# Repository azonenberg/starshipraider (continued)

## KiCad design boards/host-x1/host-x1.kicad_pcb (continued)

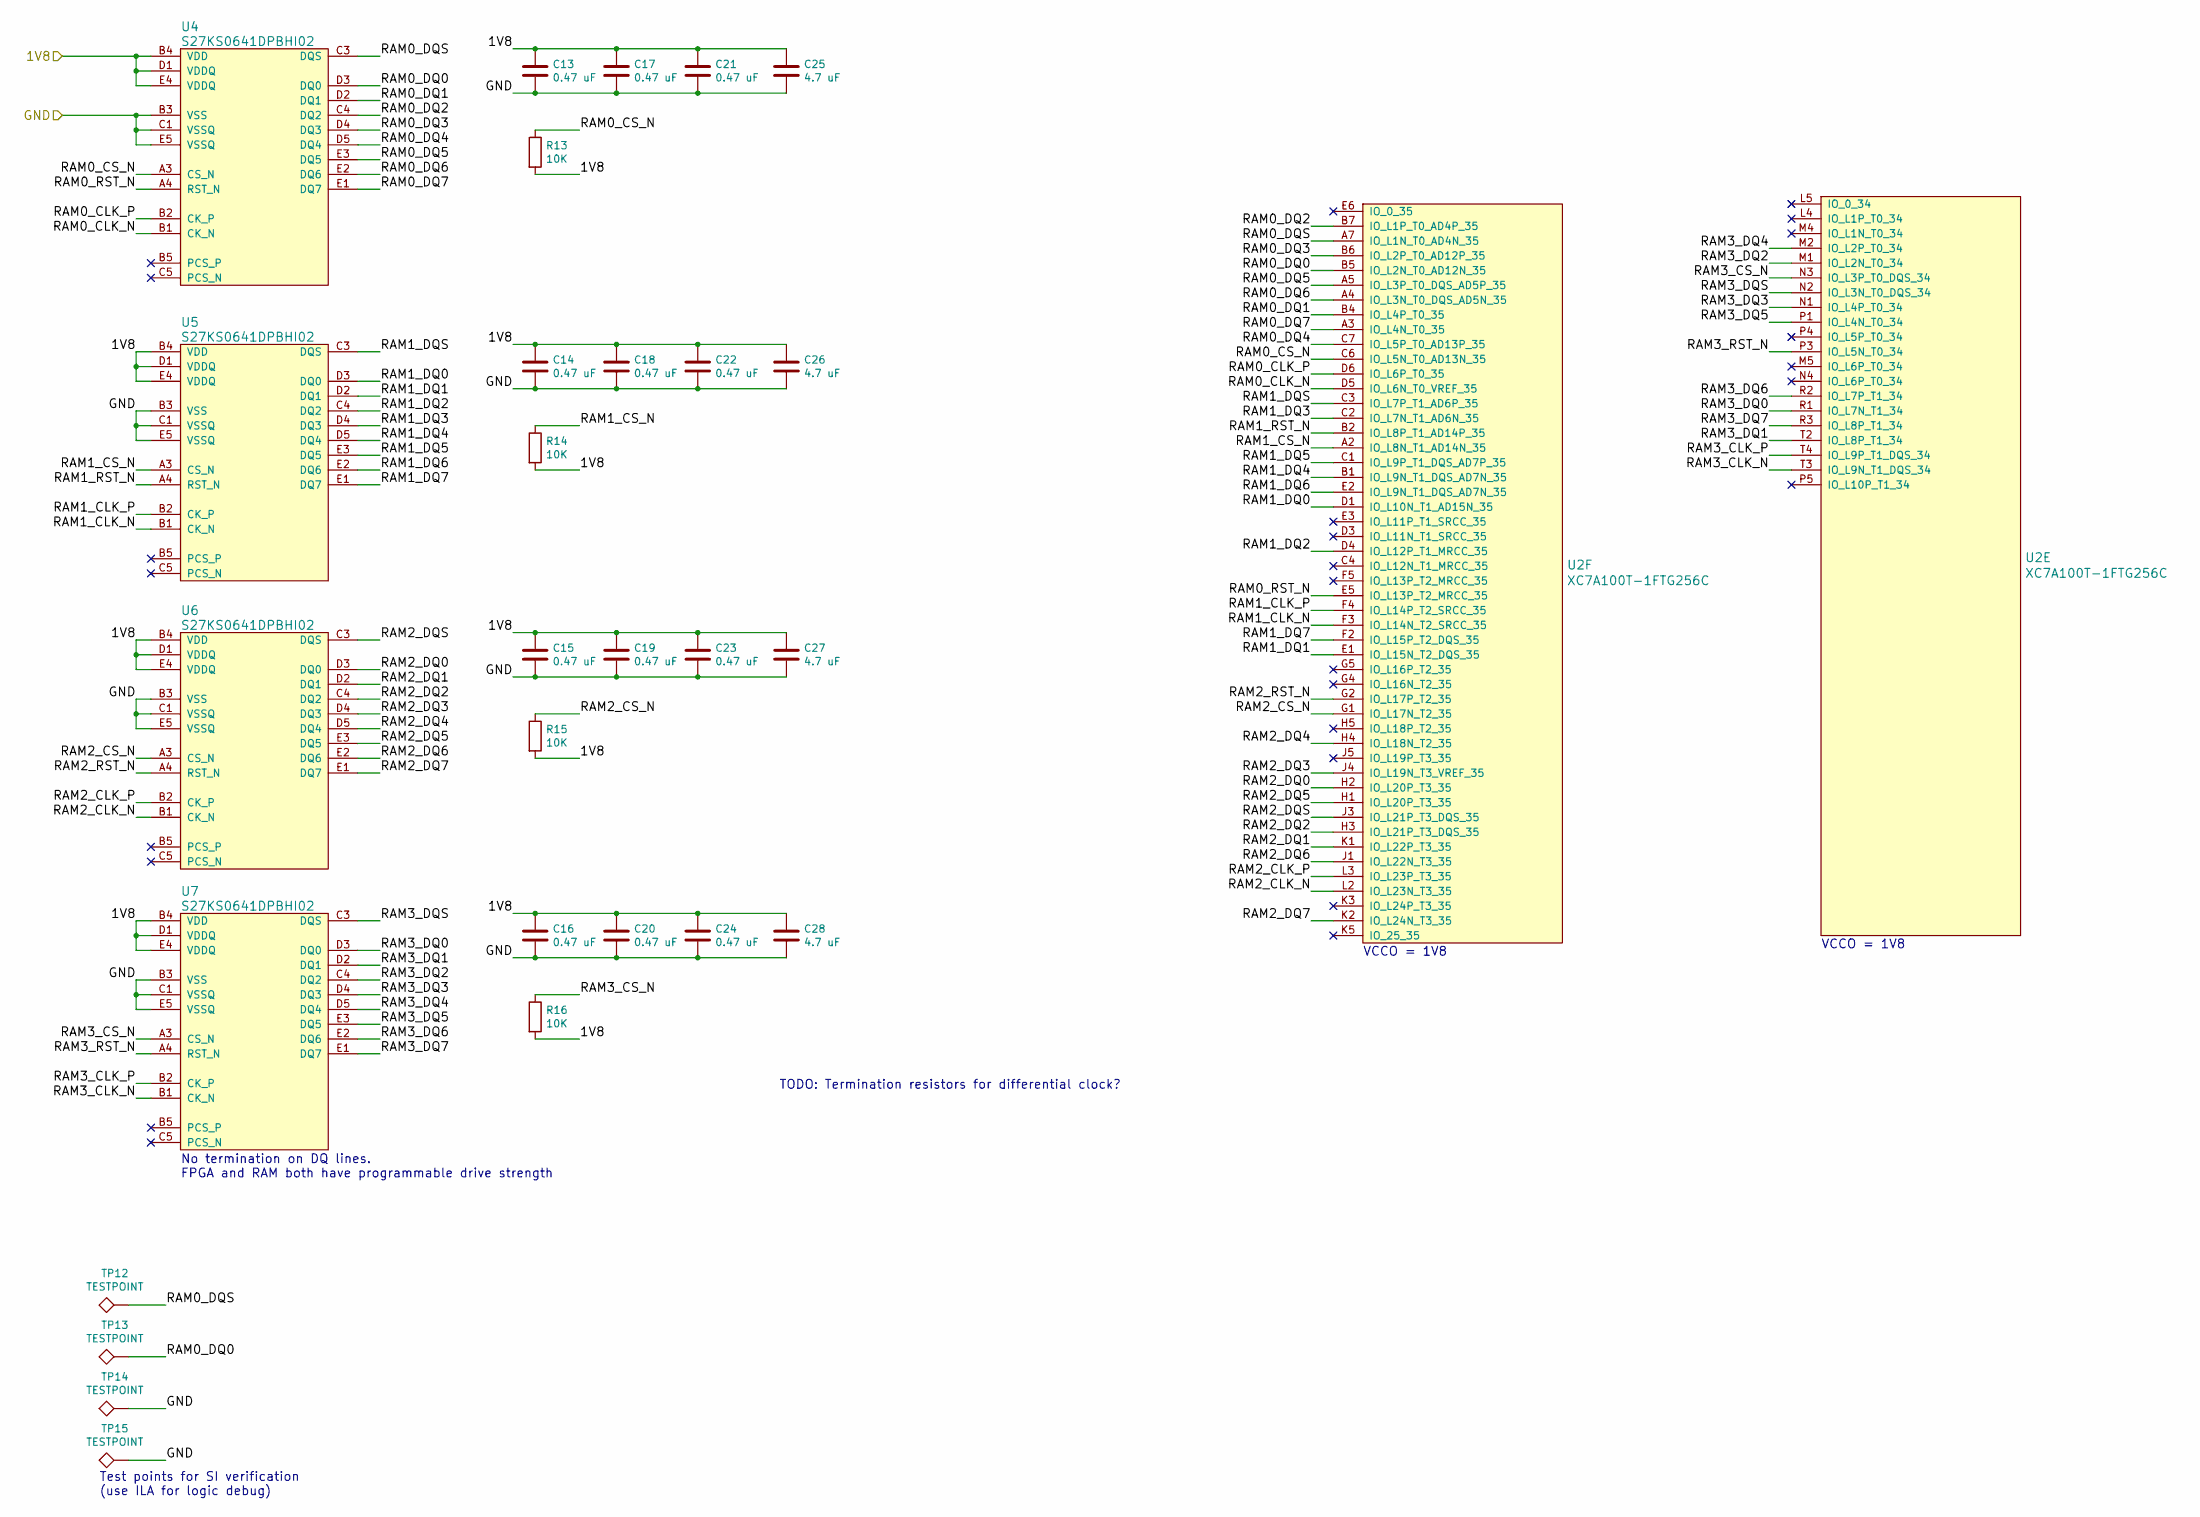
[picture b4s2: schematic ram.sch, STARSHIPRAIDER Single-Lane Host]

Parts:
C13, C14, C15, C16, C17, C18, C19, C20, C21, C22, C23, C24: 0.47 uF; EIA_0402_CAP_NOSILK
C25, C26, C27, C28: 4.7 uF; EIA_0603_CAP_NOSILK
R13, R14, R15, R16: 10K; EIA_0402_RES_NOSILK
TP12, TP13, TP14, TP15: TESTPOINT; TESTPOINT_BARETRACE_150UM
U2: XC7A100T-1FTG256C; BGA_256_17x17_FULLARRAY_1MM
U4, U5, U6, U7: S27KS0641DPBHI02; BGA_24_6x8_DEPOP1_1MM

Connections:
/1V8: C13.1, C14.1, C15.1, C16.1, C17.1, C18.1, C19.1, C20.1, C21.1, C22.1, C23.1, C24.1, C25.1, C26.1, C27.1, C28.1, R13.2, R14.2, R15.2, R16.2, U4.B4 (VDD), U4.D1 (VDDQ), U4.E4 (VDDQ), U5.B4 (VDD), U5.D1 (VDDQ), U5.E4 (VDDQ), U6.B4 (VDD), U6.D1 (VDDQ), U6.E4 (VDDQ), U7.B4 (VDD), U7.D1 (VDDQ), U7.E4 (VDDQ); also elsewhere on the board
/GND: C13.2, C14.2, C15.2, C16.2, C17.2, C18.2, C19.2, C20.2, C21.2, C22.2, C23.2, C24.2, C25.2, C26.2, C27.2, C28.2, TP14.1, TP15.1, U4.B3 (VSS), U4.C1 (VSSQ), U4.E5 (VSSQ), U5.B3 (VSS), U5.C1 (VSSQ), U5.E5 (VSSQ), U6.B3 (VSS), U6.C1 (VSSQ), U6.E5 (VSSQ), U7.B3 (VSS), U7.C1 (VSSQ), U7.E5 (VSSQ); also elsewhere on the board
/RAM/RAM0_CLK_N: U2.D5 (IO_L6N_T0_VREF_35), U4.B1 (CK_N)
/RAM/RAM0_CLK_P: U2.D6 (IO_L6P_T0_35), U4.B2 (CK_P)
/RAM/RAM0_CS_N: R13.1, U2.C6 (IO_L5N_T0_AD13N_35), U4.A3 (CS_N)
/RAM/RAM0_DQ0: TP13.1, U2.B5 (IO_L2N_T0_AD12N_35), U4.D3 (DQ0)
/RAM/RAM0_DQ1: U2.B4 (IO_L4P_T0_35), U4.D2 (DQ1)
/RAM/RAM0_DQ2: U2.B7 (IO_L1P_T0_AD4P_35), U4.C4 (DQ2)
/RAM/RAM0_DQ3: U2.B6 (IO_L2P_T0_AD12P_35), U4.D4 (DQ3)
/RAM/RAM0_DQ4: U2.C7 (IO_L5P_T0_AD13P_35), U4.D5 (DQ4)
/RAM/RAM0_DQ5: U2.A5 (IO_L3P_T0_DQS_AD5P_35), U4.E3 (DQ5)
/RAM/RAM0_DQ6: U2.A4 (IO_L3N_T0_DQS_AD5N_35), U4.E2 (DQ6)
/RAM/RAM0_DQ7: U2.A3 (IO_L4N_T0_35), U4.E1 (DQ7)
/RAM/RAM0_DQS: TP12.1, U2.A7 (IO_L1N_T0_AD4N_35), U4.C3 (DQS)
/RAM/RAM0_RST_N: U2.E5 (IO_L13P_T2_MRCC_35), U4.A4 (RST_N)
/RAM/RAM1_CLK_N: U2.F3 (IO_L14N_T2_SRCC_35), U5.B1 (CK_N)
/RAM/RAM1_CLK_P: U2.F4 (IO_L14P_T2_SRCC_35), U5.B2 (CK_P)
/RAM/RAM1_CS_N: R14.1, U2.A2 (IO_L8N_T1_AD14N_35), U5.A3 (CS_N)
/RAM/RAM1_DQ0: U2.D1 (IO_L10N_T1_AD15N_35), U5.D3 (DQ0)
/RAM/RAM1_DQ1: U2.E1 (IO_L15N_T2_DQS_35), U5.D2 (DQ1)
/RAM/RAM1_DQ2: U2.D4 (IO_L12P_T1_MRCC_35), U5.C4 (DQ2)
/RAM/RAM1_DQ3: U2.C2 (IO_L7N_T1_AD6N_35), U5.D4 (DQ3)
/RAM/RAM1_DQ4: U2.B1 (IO_L9N_T1_DQS_AD7N_35), U5.D5 (DQ4)
/RAM/RAM1_DQ5: U2.C1 (IO_L9P_T1_DQS_AD7P_35), U5.E3 (DQ5)
/RAM/RAM1_DQ6: U2.E2 (IO_L9N_T1_DQS_AD7N_35), U5.E2 (DQ6)
/RAM/RAM1_DQ7: U2.F2 (IO_L15P_T2_DQS_35), U5.E1 (DQ7)
/RAM/RAM1_DQS: U2.C3 (IO_L7P_T1_AD6P_35), U5.C3 (DQS)
/RAM/RAM1_RST_N: U2.B2 (IO_L8P_T1_AD14P_35), U5.A4 (RST_N)
/RAM/RAM2_CLK_N: U2.L2 (IO_L23N_T3_35), U6.B1 (CK_N)
/RAM/RAM2_CLK_P: U2.L3 (IO_L23P_T3_35), U6.B2 (CK_P)
/RAM/RAM2_CS_N: R15.1, U2.G1 (IO_L17N_T2_35), U6.A3 (CS_N)
/RAM/RAM2_DQ0: U2.H2 (IO_L20P_T3_35), U6.D3 (DQ0)
/RAM/RAM2_DQ1: U2.K1 (IO_L22P_T3_35), U6.D2 (DQ1)
/RAM/RAM2_DQ2: U2.H3 (IO_L21P_T3_DQS_35), U6.C4 (DQ2)
/RAM/RAM2_DQ3: U2.J4 (IO_L19N_T3_VREF_35), U6.D4 (DQ3)
/RAM/RAM2_DQ4: U2.H4 (IO_L18N_T2_35), U6.D5 (DQ4)
/RAM/RAM2_DQ5: U2.H1 (IO_L20P_T3_35), U6.E3 (DQ5)
/RAM/RAM2_DQ6: U2.J1 (IO_L22N_T3_35), U6.E2 (DQ6)
/RAM/RAM2_DQ7: U2.K2 (IO_L24N_T3_35), U6.E1 (DQ7)
/RAM/RAM2_DQS: U2.J3 (IO_L21P_T3_DQS_35), U6.C3 (DQS)
/RAM/RAM2_RST_N: U2.G2 (IO_L17P_T2_35), U6.A4 (RST_N)
/RAM/RAM3_CLK_N: U2.T3 (IO_L9N_T1_DQS_34), U7.B1 (CK_N)
/RAM/RAM3_CLK_P: U2.T4 (IO_L9P_T1_DQS_34), U7.B2 (CK_P)
/RAM/RAM3_CS_N: R16.1, U2.N3 (IO_L3P_T0_DQS_34), U7.A3 (CS_N)
/RAM/RAM3_DQ0: U2.R1 (IO_L7N_T1_34), U7.D3 (DQ0)
/RAM/RAM3_DQ1: U2.T2 (IO_L8P_T1_34), U7.D2 (DQ1)
/RAM/RAM3_DQ2: U2.M1 (IO_L2N_T0_34), U7.C4 (DQ2)
/RAM/RAM3_DQ3: U2.N1 (IO_L4P_T0_34), U7.D4 (DQ3)
/RAM/RAM3_DQ4: U2.M2 (IO_L2P_T0_34), U7.D5 (DQ4)
/RAM/RAM3_DQ5: U2.P1 (IO_L4N_T0_34), U7.E3 (DQ5)
/RAM/RAM3_DQ6: U2.R2 (IO_L7P_T1_34), U7.E2 (DQ6)
/RAM/RAM3_DQ7: U2.R3 (IO_L8P_T1_34), U7.E1 (DQ7)
/RAM/RAM3_DQS: U2.N2 (IO_L3N_T0_DQS_34), U7.C3 (DQS)
/RAM/RAM3_RST_N: U2.P3 (IO_L5N_T0_34), U7.A4 (RST_N)

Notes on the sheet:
VCCO = 1V8
No termination on DQ lines. FPGA and RAM both have programmable drive strength
Test points for SI verification (use ILA for logic debug)
TODO: Termination resistors for differential clock?

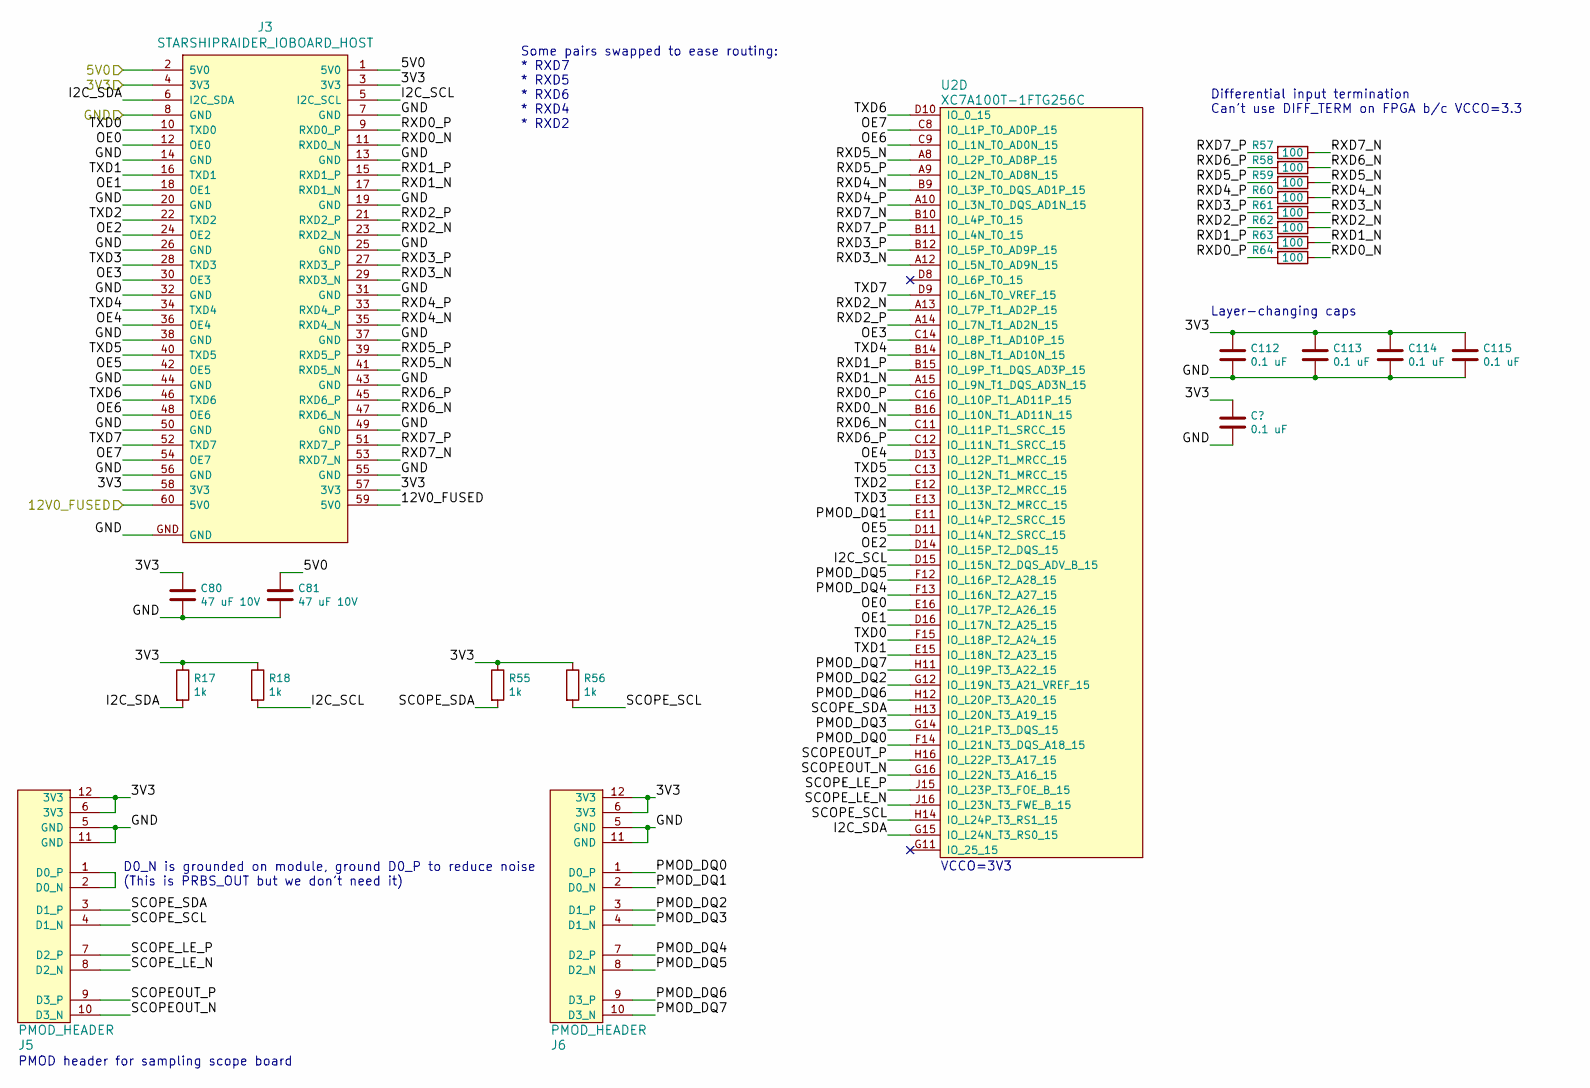
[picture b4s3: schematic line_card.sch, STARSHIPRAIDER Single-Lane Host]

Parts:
C80, C81: 47 uF 10V; EIA_1210_CAP_NOSILK
C112, C113, C114, C115: 0.1 uF; EIA_0402_CAP_NOSILK
J3: STARSHIPRAIDER_IOBOARD_HOST; CONN_SAMTEC_QTH-030-01-L-D-A
J5, J6: PMOD_HEADER; CONN_HEADER_2.54MM_2x6_RA_PMOD_HOST
R17, R18, R55, R56: 1k; EIA_0402_RES_NOSILK
R57, R58, R59, R60, R61, R62, R63, R64: 100; EIA_0201_RES_NOSILK
U2: XC7A100T-1FTG256C; BGA_256_17x17_FULLARRAY_1MM

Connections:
/3V3: C80.1, C112.1, C113.1, C114.1, C115.1, J3.3 (3V3), J3.4 (3V3), J3.57 (3V3), J3.58 (3V3), J5.6 (3V3), J5.12 (3V3), J6.6 (3V3), J6.12 (3V3), R17.1, R18.1, R55.1, R56.1; also elsewhere on the board
/5V0: C81.1, J3.1 (5V0), J3.2 (5V0); also elsewhere on the board
/12V0_FUSED: J3.59 (5V0), J3.60 (5V0); also elsewhere on the board
/GND: C80.2, C81.2, C112.2, C113.2, C114.2, C115.2, J3.7 (GND), J3.8 (GND), J3.13 (GND), J3.14 (GND), J3.19 (GND), J3.20 (GND), J3.25 (GND), J3.26 (GND), J3.31 (GND), J3.32 (GND), J3.37 (GND), J3.38 (GND), J3.43 (GND), J3.44 (GND), J3.49 (GND), J3.50 (GND), J3.55 (GND), J3.56 (GND), J3.GND, J5.5 (GND), J5.11 (GND), J6.5 (GND), J6.11 (GND); also elsewhere on the board
/Line Card/I2C_SCL: J3.5 (I2C_SCL), R18.2, U2.D15 (IO_L15N_T2_DQS_ADV_B_15)
/Line Card/I2C_SDA: J3.6 (I2C_SDA), R17.2, U2.G15 (IO_L24N_T3_RS0_15)
/Line Card/OE0: J3.12 (OE0), U2.E16 (IO_L17P_T2_A26_15)
/Line Card/OE1: J3.18 (OE1), U2.D16 (IO_L17N_T2_A25_15)
/Line Card/OE2: J3.24 (OE2), U2.D14 (IO_L15P_T2_DQS_15)
/Line Card/OE3: J3.30 (OE3), U2.C14 (IO_L8P_T1_AD10P_15)
/Line Card/OE4: J3.36 (OE4), U2.D13 (IO_L12P_T1_MRCC_15)
/Line Card/OE5: J3.42 (OE5), U2.D11 (IO_L14N_T2_SRCC_15)
/Line Card/OE6: J3.48 (OE6), U2.C9 (IO_L1N_T0_AD0N_15)
/Line Card/OE7: J3.54 (OE7), U2.C8 (IO_L1P_T0_AD0P_15)
/Line Card/PMOD_DQ0: J6.1 (D0_P), U2.F14 (IO_L21N_T3_DQS_A18_15)
/Line Card/PMOD_DQ1: J6.2 (D0_N), U2.E11 (IO_L14P_T2_SRCC_15)
/Line Card/PMOD_DQ2: J6.3 (D1_P), U2.G12 (IO_L19N_T3_A21_VREF_15)
/Line Card/PMOD_DQ3: J6.4 (D1_N), U2.G14 (IO_L21P_T3_DQS_15)
/Line Card/PMOD_DQ4: J6.7 (D2_P), U2.F13 (IO_L16N_T2_A27_15)
/Line Card/PMOD_DQ5: J6.8 (D2_N), U2.F12 (IO_L16P_T2_A28_15)
/Line Card/PMOD_DQ6: J6.9 (D3_P), U2.H12 (IO_L20P_T3_A20_15)
/Line Card/PMOD_DQ7: J6.10 (D3_N), U2.H11 (IO_L19P_T3_A22_15)
/Line Card/RXD0_N: J3.11 (RXD0_N), R64.1, U2.B16 (IO_L10N_T1_AD11N_15)
/Line Card/RXD0_P: J3.9 (RXD0_P), R64.2, U2.C16 (IO_L10P_T1_AD11P_15)
/Line Card/RXD1_N: J3.17 (RXD1_N), R63.1, U2.A15 (IO_L9N_T1_DQS_AD3N_15)
/Line Card/RXD1_P: J3.15 (RXD1_P), R63.2, U2.B15 (IO_L9P_T1_DQS_AD3P_15)
/Line Card/RXD2_N: J3.23 (RXD2_N), R62.1, U2.A13 (IO_L7P_T1_AD2P_15)
/Line Card/RXD2_P: J3.21 (RXD2_P), R62.2, U2.A14 (IO_L7N_T1_AD2N_15)
/Line Card/RXD3_N: J3.29 (RXD3_N), R61.1, U2.A12 (IO_L5N_T0_AD9N_15)
/Line Card/RXD3_P: J3.27 (RXD3_P), R61.2, U2.B12 (IO_L5P_T0_AD9P_15)
/Line Card/RXD4_N: J3.35 (RXD4_N), R60.1, U2.B9 (IO_L3P_T0_DQS_AD1P_15)
/Line Card/RXD4_P: J3.33 (RXD4_P), R60.2, U2.A10 (IO_L3N_T0_DQS_AD1N_15)
/Line Card/RXD5_N: J3.41 (RXD5_N), R59.1, U2.A8 (IO_L2P_T0_AD8P_15)
/Line Card/RXD5_P: J3.39 (RXD5_P), R59.2, U2.A9 (IO_L2N_T0_AD8N_15)
/Line Card/RXD6_N: J3.47 (RXD6_N), R58.1, U2.C11 (IO_L11P_T1_SRCC_15)
/Line Card/RXD6_P: J3.45 (RXD6_P), R58.2, U2.C12 (IO_L11N_T1_SRCC_15)
/Line Card/RXD7_N: J3.53 (RXD7_N), R57.1, U2.B10 (IO_L4P_T0_15)
/Line Card/RXD7_P: J3.51 (RXD7_P), R57.2, U2.B11 (IO_L4N_T0_15)
/Line Card/SCOPEOUT_N: J5.10 (D3_N), U2.G16 (IO_L22N_T3_A16_15)
/Line Card/SCOPEOUT_P: J5.9 (D3_P), U2.H16 (IO_L22P_T3_A17_15)
/Line Card/SCOPE_LE_N: J5.8 (D2_N), U2.J16 (IO_L23N_T3_FWE_B_15)
/Line Card/SCOPE_LE_P: J5.7 (D2_P), U2.J15 (IO_L23P_T3_FOE_B_15)
/Line Card/SCOPE_SCL: J5.4 (D1_N), R56.2, U2.H14 (IO_L24P_T3_RS1_15)
/Line Card/SCOPE_SDA: J5.3 (D1_P), R55.2, U2.H13 (IO_L20N_T3_A19_15)
/Line Card/TXD0: J3.10 (TXD0), U2.F15 (IO_L18P_T2_A24_15)
/Line Card/TXD1: J3.16 (TXD1), U2.E15 (IO_L18N_T2_A23_15)
/Line Card/TXD2: J3.22 (TXD2), U2.E12 (IO_L13P_T2_MRCC_15)
/Line Card/TXD3: J3.28 (TXD3), U2.E13 (IO_L13N_T2_MRCC_15)
/Line Card/TXD4: J3.34 (TXD4), U2.B14 (IO_L8N_T1_AD10N_15)
/Line Card/TXD5: J3.40 (TXD5), U2.C13 (IO_L12N_T1_MRCC_15)
/Line Card/TXD6: J3.46 (TXD6), U2.D10 (IO_0_15)
/Line Card/TXD7: J3.52 (TXD7), U2.D9 (IO_L6N_T0_VREF_15)
unnamed: J5.1 (D0_P), J5.2 (D0_N)

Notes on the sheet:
VCCO=3V3
PMOD header for sampling scope board
D0_N is grounded on module, ground D0_P to reduce noise (This is PRBS_OUT but we don't need it)
Some pairs swapped to ease routing: * RXD7 * RXD5 * RXD6 * RXD4 * RXD2
Differential input termination Can't use DIFF_TERM on FPGA b/c VCCO=3.3
Layer-changing caps

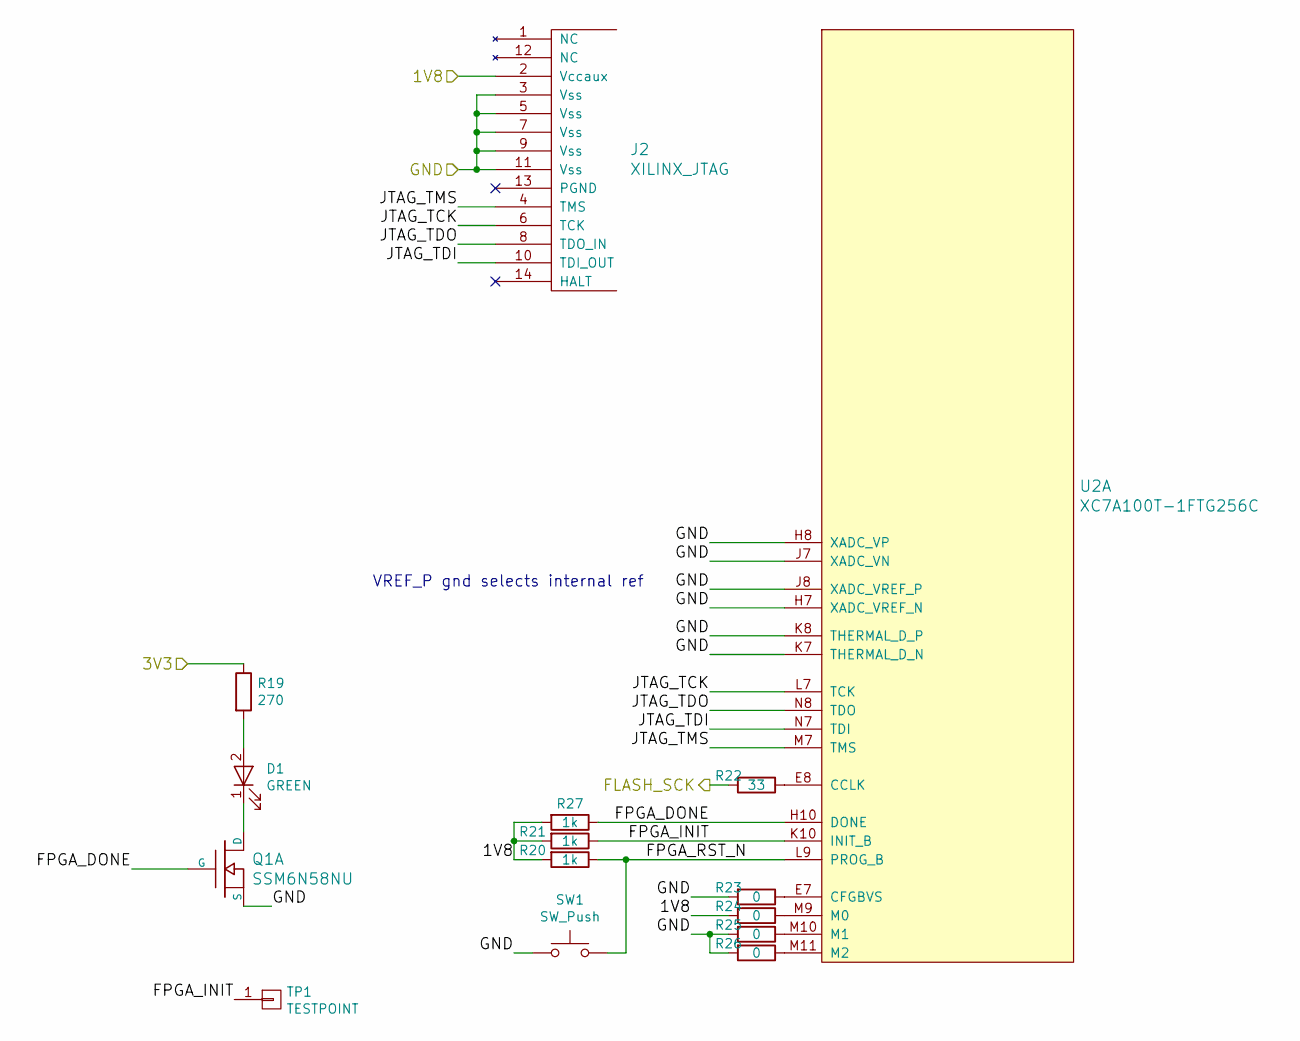
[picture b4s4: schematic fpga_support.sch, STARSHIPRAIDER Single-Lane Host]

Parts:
D1: GREEN; EIA_0603_LED
J2: XILINX_JTAG; XILINX_JTAG_PTH_MOLEX_0878311420
Q1: SSM6N58NU; DFN_6_0.65MM_2x2MM_GDS
R19: 270; EIA_0402_RES_NOSILK
R20, R21, R27: 1k; EIA_0402_RES_NOSILK
R22: 33; EIA_0402_RES_NOSILK
R23, R24, R25, R26: 0; EIA_0402_RES_NOSILK
SW1: SW_Push; SWITCH_RAFI_MICON_5
TP1: TESTPOINT; TESTPOINT_SMT_0.5MM
U2: XC7A100T-1FTG256C; BGA_256_17x17_FULLARRAY_1MM

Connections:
/1V8: J2.2 (Vccaux), R20.2, R21.2, R24.2, R27.2; also elsewhere on the board
/3V3: R19.1; also elsewhere on the board
/FLASH_SCK: R22.2; also elsewhere on the board
/FPGA support/FPGA_DONE: Q1.G1 (G), R27.1, U2.H10 (DONE)
/FPGA support/FPGA_INIT: R21.1, TP1.1, U2.K10 (INIT_B)
/FPGA support/FPGA_RST_N: R20.1, SW1.2, U2.L9 (PROG_B)
/FPGA support/JTAG_TCK: J2.6 (TCK), U2.L7 (TCK)
/FPGA support/JTAG_TDI: J2.10 (TDI_OUT), U2.N7 (TDI)
/FPGA support/JTAG_TDO: J2.8 (TDO_IN), U2.N8 (TDO)
/FPGA support/JTAG_TMS: J2.4 (TMS), U2.M7 (TMS)
/GND: J2.3 (Vss), J2.5 (Vss), J2.7 (Vss), J2.9 (Vss), J2.11 (Vss), Q1.S1 (S), R23.2, R25.2, R26.2, SW1.1, U2.H7 (XADC_VREF_N), U2.H8 (XADC_VP), U2.J7 (XADC_VN), U2.J8 (XADC_VREF_P), U2.K7 (THERMAL_D_N), U2.K8 (THERMAL_D_P); also elsewhere on the board
unnamed: D1.1 (K), Q1.D1 (D)
unnamed: D1.2 (A), R19.2
unnamed: R22.1, U2.E8 (CCLK)
unnamed: R23.1, U2.E7 (CFGBVS)
unnamed: R24.1, U2.M9 (M0)
unnamed: R25.1, U2.M10 (M1)
unnamed: R26.1, U2.M11 (M2)

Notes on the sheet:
VREF_P gnd selects internal ref

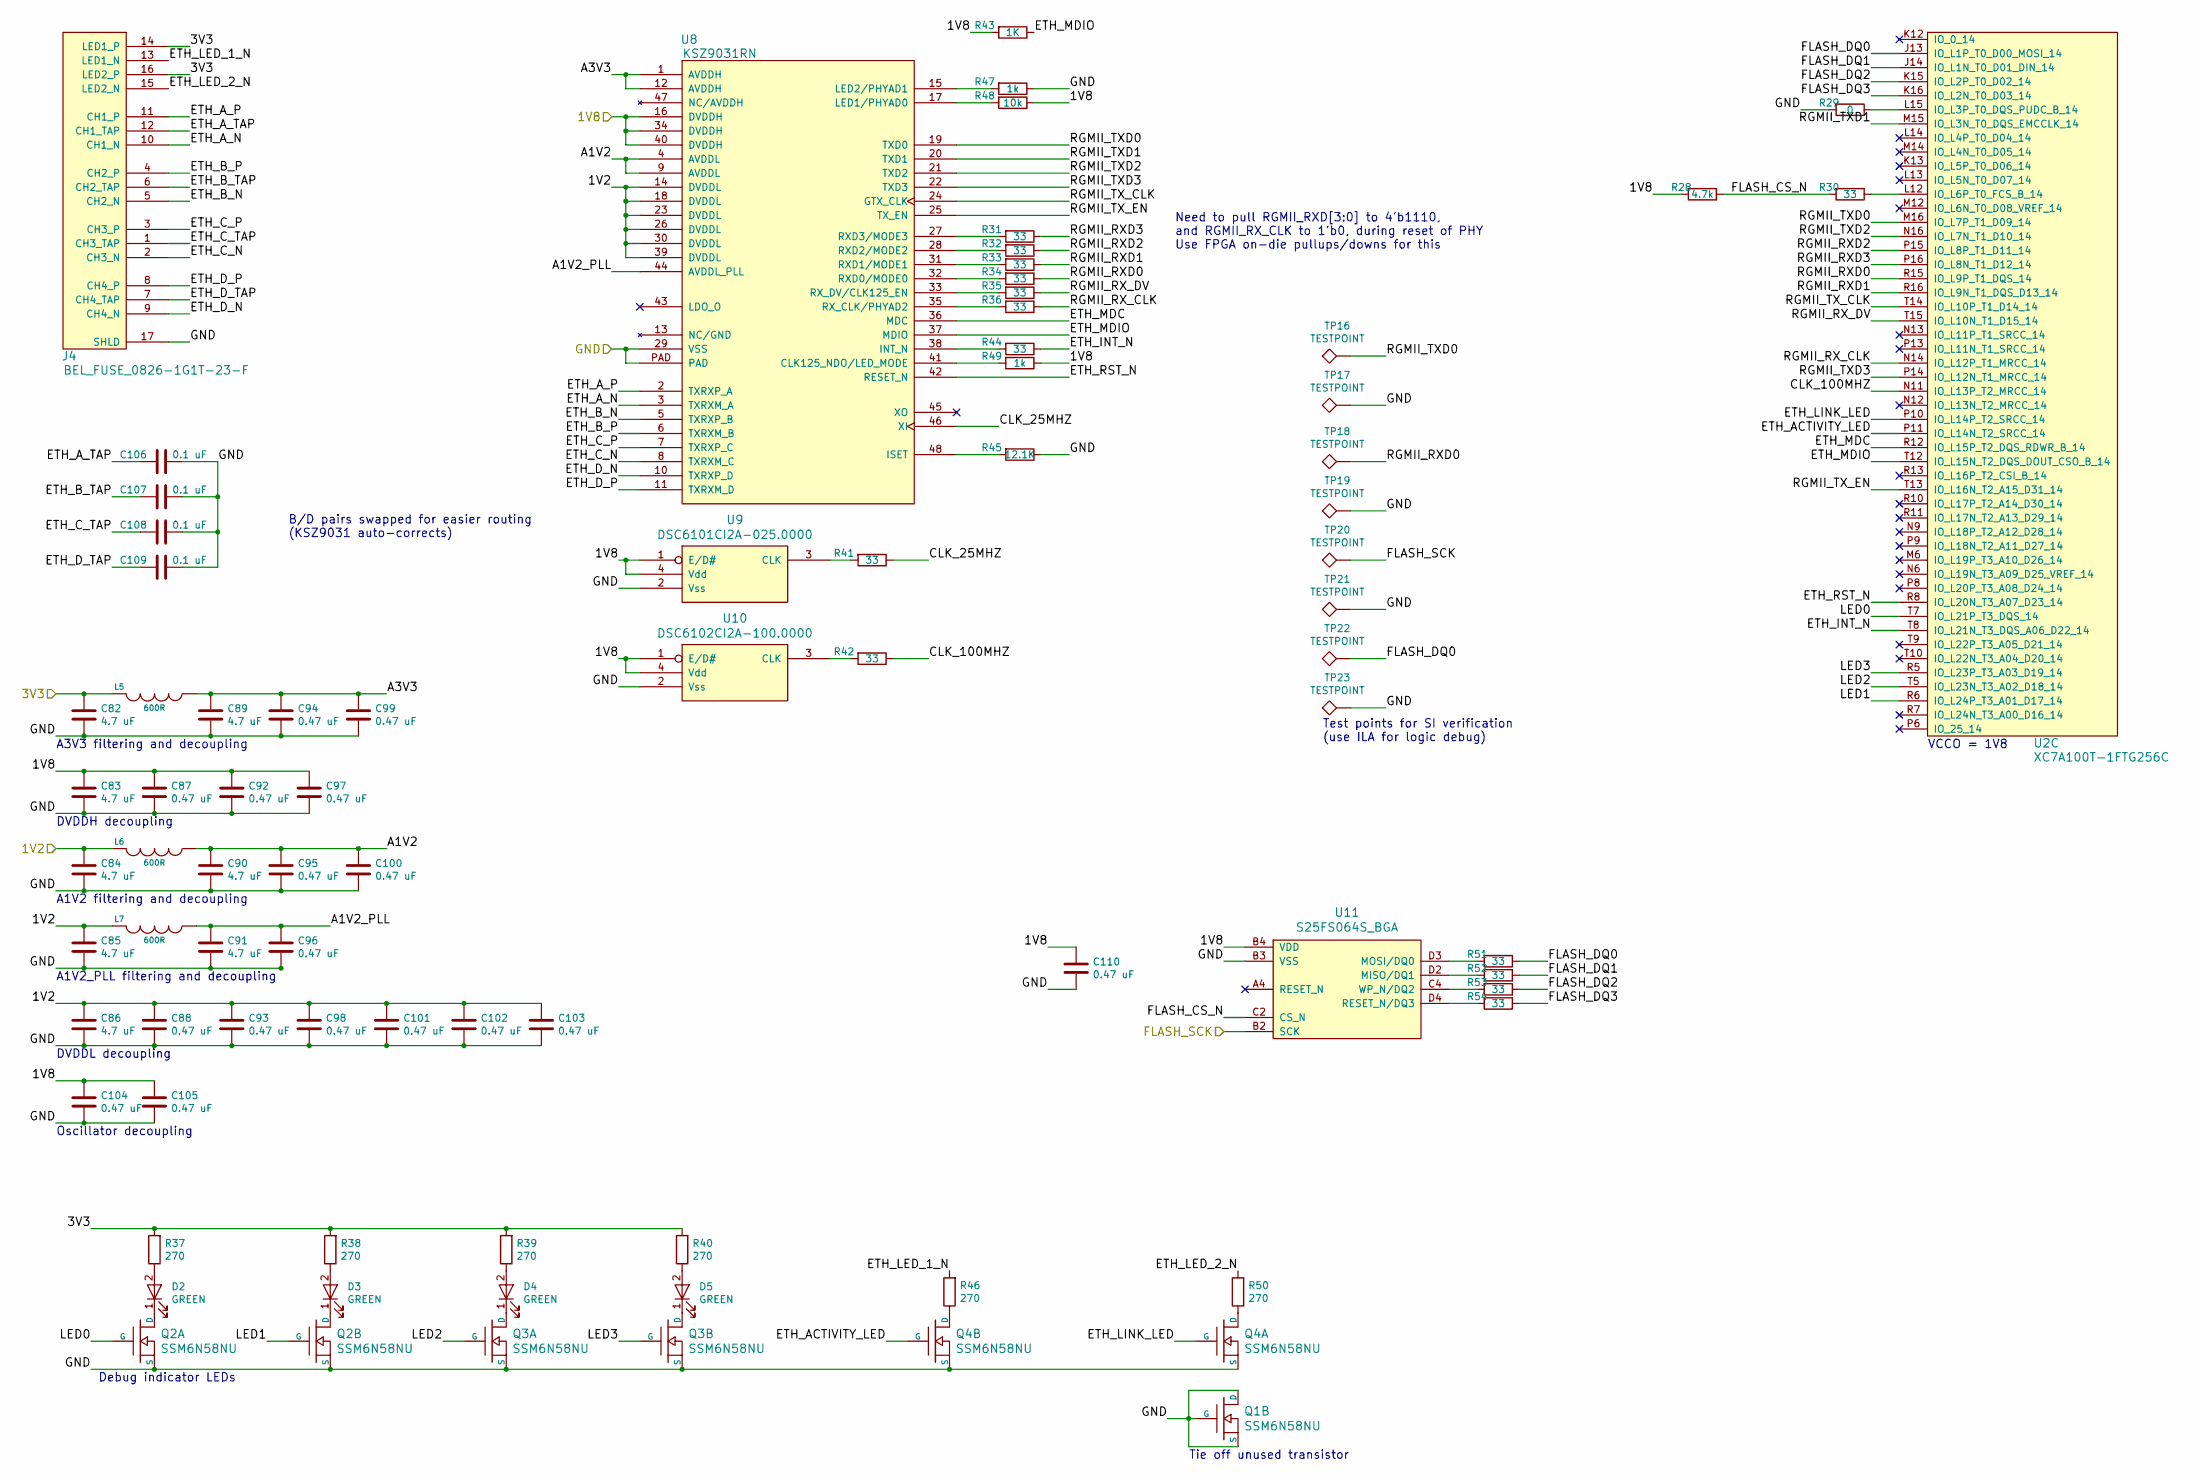
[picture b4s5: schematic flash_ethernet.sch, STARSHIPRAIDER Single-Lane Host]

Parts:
C82, C83, C84, C85, C86, C89, C90, C91: 4.7 uF; EIA_0603_CAP_NOSILK
C87, C88, C92, C93, C94, C95, C96, C97, C98, C99, C100, C101, C102, C103, C104, C105, C110: 0.47 uF; EIA_0402_CAP_NOSILK
C106, C107, C108, C109: 0.1 uF; EIA_0402_CAP_NOSILK
D2, D3, D4, D5: GREEN; EIA_0603_LED
J4: BEL_FUSE_0826-1G1T-23-F; CONN_BELFUSE_0826_1G1T_23_F
L5, L6, L7: 600R; EIA_0402_RES_NOSILK
Q1, Q2, Q3, Q4: SSM6N58NU; DFN_6_0.65MM_2x2MM_GDS
R28: 4.7k; EIA_0402_RES_NOSILK
R29: 0; EIA_0402_RES_NOSILK
R30, R31, R32, R33, R34, R35, R36, R41, R42, R44, R51, R52, R53, R54: 33; EIA_0402_RES_NOSILK
R37, R38, R39, R40, R46, R50: 270; EIA_0402_RES_NOSILK
R43: 1K; EIA_0402_RES_NOSILK
R45: 12.1K; EIA_0402_RES_NOSILK
R47, R49: 1k; EIA_0402_RES_NOSILK
R48: 10k; EIA_0402_RES_NOSILK
TP16, TP17, TP18, TP19, TP20, TP21, TP22, TP23: TESTPOINT; TESTPOINT_BARETRACE_150UM
U2: XC7A100T-1FTG256C; BGA_256_17x17_FULLARRAY_1MM
U8: KSZ9031RN; QFN_48_0.5MM_7x7MM
U9: DSC6101CI2A-025.0000; OSCILLATOR_3.2x2.5
U10: DSC6102CI2A-100.0000; OSCILLATOR_3.2x2.5
U11: S25FS064S_BGA; BGA_24_6x8_DEPOP1_1MM

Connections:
/1V2: C84.1, C85.1, C86.1, C88.1, C93.1, C98.1, C101.1, C102.1, C103.1, L6.2, L7.2, U8.14 (DVDDL), U8.18 (DVDDL), U8.23 (DVDDL), U8.26 (DVDDL), U8.30 (DVDDL), U8.39 (DVDDL); also elsewhere on the board
/1V8: C83.1, C87.1, C92.1, C97.1, C104.1, C105.1, C110.1, R28.2, R43.2, R48.1, R49.1, U8.16 (DVDDH), U8.34 (DVDDH), U8.40 (DVDDH), U9.1 (E/D#), U9.4 (Vdd), U10.1 (E/D#), U10.4 (Vdd), U11.B4 (VDD); also elsewhere on the board
/3V3: C82.1, J4.14 (LED1_P), J4.16 (LED2_P), L5.2, R37.2, R38.2, R39.2, R40.2; also elsewhere on the board
/FLASH_SCK: TP20.1, U11.B2 (SCK); also elsewhere on the board
/Flash / Ethernet/A1V2: C90.1, C95.1, C100.1, L6.1, U8.4 (AVDDL), U8.9 (AVDDL)
/Flash / Ethernet/A1V2_PLL: C91.1, C96.1, L7.1, U8.44 (AVDDL_PLL)
/Flash / Ethernet/A3V3: C89.1, C94.1, C99.1, L5.1, U8.1 (AVDDH), U8.12 (AVDDH)
/Flash / Ethernet/CLK_25MHZ: R41.1, U8.46 (XI)
/Flash / Ethernet/CLK_100MHZ: R42.1, U2.N11 (IO_L13P_T2_MRCC_14)
/Flash / Ethernet/ETH_ACTIVITY_LED: Q4.G2 (G), U2.P11 (IO_L14N_T2_SRCC_14)
/Flash / Ethernet/ETH_A_N: J4.10 (CH1_N), U8.3 (TXRXM_A)
/Flash / Ethernet/ETH_A_P: J4.11 (CH1_P), U8.2 (TXRXP_A)
/Flash / Ethernet/ETH_A_TAP: C106.1, J4.12 (CH1_TAP)
/Flash / Ethernet/ETH_B_N: J4.5 (CH2_N), U8.5 (TXRXP_B)
/Flash / Ethernet/ETH_B_P: J4.4 (CH2_P), U8.6 (TXRXM_B)
/Flash / Ethernet/ETH_B_TAP: C107.1, J4.6 (CH2_TAP)
/Flash / Ethernet/ETH_C_N: J4.2 (CH3_N), U8.8 (TXRXM_C)
/Flash / Ethernet/ETH_C_P: J4.3 (CH3_P), U8.7 (TXRXP_C)
/Flash / Ethernet/ETH_C_TAP: C108.1, J4.1 (CH3_TAP)
/Flash / Ethernet/ETH_D_N: J4.9 (CH4_N), U8.10 (TXRXP_D)
/Flash / Ethernet/ETH_D_P: J4.8 (CH4_P), U8.11 (TXRXM_D)
/Flash / Ethernet/ETH_D_TAP: C109.1, J4.7 (CH4_TAP)
/Flash / Ethernet/ETH_INT_N: R44.1, U2.T8 (IO_L21N_T3_DQS_A06_D22_14)
/Flash / Ethernet/ETH_LED_1_N: J4.13 (LED1_N), R46.2
/Flash / Ethernet/ETH_LED_2_N: J4.15 (LED2_N), R50.2
/Flash / Ethernet/ETH_LINK_LED: Q4.G1 (G), U2.P10 (IO_L14P_T2_SRCC_14)
/Flash / Ethernet/ETH_MDC: U2.R12 (IO_L15P_T2_DQS_RDWR_B_14), U8.36 (MDC)
/Flash / Ethernet/ETH_MDIO: R43.1, U2.T12 (IO_L15N_T2_DQS_DOUT_CSO_B_14), U8.37 (MDIO)
/Flash / Ethernet/ETH_RST_N: U2.R8 (IO_L20N_T3_A07_D23_14), U8.42 (RESET_N)
/Flash / Ethernet/FLASH_CS_N: R28.1, R30.2, U11.C2 (CS_N)
/Flash / Ethernet/FLASH_DQ0: R51.1, TP22.1, U2.J13 (IO_L1P_T0_D00_MOSI_14)
/Flash / Ethernet/FLASH_DQ1: R52.1, U2.J14 (IO_L1N_T0_D01_DIN_14)
/Flash / Ethernet/FLASH_DQ2: R53.1, U2.K15 (IO_L2P_T0_D02_14)
/Flash / Ethernet/FLASH_DQ3: R54.1, U2.K16 (IO_L2N_T0_D03_14)
/Flash / Ethernet/LED0: Q2.G1 (G), U2.T7 (IO_L21P_T3_DQS_14)
/Flash / Ethernet/LED1: Q2.G2 (G), U2.R6 (IO_L24P_T3_A01_D17_14)
/Flash / Ethernet/LED2: Q3.G1 (G), U2.T5 (IO_L23N_T3_A02_D18_14)
/Flash / Ethernet/LED3: Q3.G2 (G), U2.R5 (IO_L23P_T3_A03_D19_14)
/Flash / Ethernet/RGMII_RXD0: R34.1, TP18.1, U2.R15 (IO_L9P_T1_DQS_14)
/Flash / Ethernet/RGMII_RXD1: R33.1, U2.R16 (IO_L9N_T1_DQS_D13_14)
/Flash / Ethernet/RGMII_RXD2: R32.1, U2.P15 (IO_L8P_T1_D11_14)
/Flash / Ethernet/RGMII_RXD3: R31.1, U2.P16 (IO_L8N_T1_D12_14)
/Flash / Ethernet/RGMII_RX_CLK: R36.1, U2.N14 (IO_L12P_T1_MRCC_14)
/Flash / Ethernet/RGMII_RX_DV: R35.1, U2.T15 (IO_L10N_T1_D15_14)
/Flash / Ethernet/RGMII_TXD0: TP16.1, U2.M16 (IO_L7P_T1_D09_14), U8.19 (TXD0)
/Flash / Ethernet/RGMII_TXD1: U2.M15 (IO_L3N_T0_DQS_EMCCLK_14), U8.20 (TXD1)
/Flash / Ethernet/RGMII_TXD2: U2.N16 (IO_L7N_T1_D10_14), U8.21 (TXD2)
/Flash / Ethernet/RGMII_TXD3: U2.P14 (IO_L12N_T1_MRCC_14), U8.22 (TXD3)
/Flash / Ethernet/RGMII_TX_CLK: U2.T14 (IO_L10P_T1_D14_14), U8.24 (GTX_CLK)
/Flash / Ethernet/RGMII_TX_EN: U2.T13 (IO_L16N_T2_A15_D31_14), U8.25 (TX_EN)
/GND: C82.2, C83.2, C84.2, C85.2, C86.2, C87.2, C88.2, C89.2, C90.2, C91.2, C92.2, C93.2, C94.2, C95.2, C96.2, C97.2, C98.2, C99.2, C100.2, C101.2, C102.2, C103.2, C104.2, C105.2, C106.2, C107.2, C108.2, C109.2, C110.2, J4.17 (SHLD), Q1.D2 (D), Q1.G2 (G), Q1.S2 (S), Q2.S1 (S), Q2.S2 (S), Q3.S1 (S), Q3.S2 (S), Q4.S1 (S), Q4.S2 (S), R29.2, R45.1, R47.1, TP17.1, TP19.1, TP21.1, TP23.1, U8.29 (VSS), U8.PAD, U9.2 (Vss), U10.2 (Vss), U11.B3 (VSS); also elsewhere on the board
unnamed: D2.1 (K), Q2.D1 (D)
unnamed: D2.2 (A), R37.1
unnamed: D3.1 (K), Q2.D2 (D)
unnamed: D3.2 (A), R38.1
unnamed: D4.1 (K), Q3.D1 (D)
unnamed: D4.2 (A), R39.1
unnamed: D5.1 (K), Q3.D2 (D)
unnamed: D5.2 (A), R40.1
unnamed: Q4.D1 (D), R50.1
unnamed: Q4.D2 (D), R46.1
unnamed: R29.1, U2.L15 (IO_L3P_T0_DQS_PUDC_B_14)
unnamed: R30.1, U2.L12 (IO_L6P_T0_FCS_B_14)
unnamed: R31.2, U8.27 (RXD3/MODE3)
unnamed: R32.2, U8.28 (RXD2/MODE2)
unnamed: R33.2, U8.31 (RXD1/MODE1)
unnamed: R34.2, U8.32 (RXD0/MODE0)
unnamed: R35.2, U8.33 (RX_DV/CLK125_EN)
unnamed: R36.2, U8.35 (RX_CLK/PHYAD2)
unnamed: R41.2, U9.3 (CLK)
unnamed: R42.2, U10.3 (CLK)
unnamed: R44.2, U8.38 (INT_N)
unnamed: R45.2, U8.48 (ISET)
unnamed: R47.2, U8.15 (LED2/PHYAD1)
unnamed: R48.2, U8.17 (LED1/PHYAD0)
unnamed: R49.2, U8.41 (CLK125_NDO/LED_MODE)
unnamed: R51.2, U11.D3 (MOSI/DQ0)
unnamed: R52.2, U11.D2 (MISO/DQ1)
unnamed: R53.2, U11.C4 (WP_N/DQ2)
unnamed: R54.2, U11.D4 (RESET_N/DQ3)

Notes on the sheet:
A3V3 filtering and decoupling
DVDDH decoupling
A1V2 filtering and decoupling
A1V2_PLL filtering and decoupling
DVDDL decoupling
Debug indicator LEDs
Oscillator decoupling
VCCO = 1V8
Need to pull RGMII_RXD[3:0] to 4'b1110, and RGMII_RX_CLK to 1'b0, during reset of PHY Use FPGA on-die pullups/downs for this
Test points for SI verification (use ILA for logic debug)
Tie off unused transistor
B/D pairs swapped for easier routing (KSZ9031 auto-corrects)
